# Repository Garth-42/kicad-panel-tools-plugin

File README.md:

# harness_engine

Generate wire-harness manufacturing docs from a KiCad design: a point-to-point
**wire list** (CSV), a **WireViz** harness diagram/BOM, and a **panel wiring
diagram** (SVG) drawn from the board itself — device outlines, wire-colored
runs, wire-number flags. The schematic/board stays the single source of truth;
the docs are generated, never hand-maintained.

Also in the box: a KiCad **project template** for 1:1 panel layouts (net
classes as wire types, colored/width-scaled tracks), the **Panel device**
footprint wizard + starter library for fast 2D device footprints, persistent
wire numbers, and a **PCM package** (`scripts/build_pcm.py`) for one-click
install. No third-party Python packages required (YAML reader bundled).

## Docs

**User guide** (GitHub Pages site, source in `docs/`):
[index](docs/index.md) · [installation](docs/installation.md) ·
[KiCad project setup / naming conventions](docs/kicad-setup.md) ·
[exporting CSV & WireViz](docs/exporting.md).
To host it: repo **Settings → Pages → Deploy from a branch → `main` + `/docs`**.

Developer docs:

- **`CLAUDE.md`** — architecture, conventions, testing, and the tested-vs-unverified matrix.
  Start here (also the Claude Code context file).
- **`docs/SPEC_SCHEMA.md`** — full `harness_specs.yaml` reference.
- **`docs/FREECAD_ROADMAP.md`** — the planned 3D / cut-length / formboard expansion.
- **`kicad_plugin/README.md`** — installing and using the pcbnew plugin.

## Two ways to run

**Board route** (pcbnew Action Plugin) — needs footprints; the only route that yields real
cut lengths. Copy `kicad_plugin/` and `harness/` into your KiCad plugin directory
(Tools → External Plugins → Open Plugin Directory), Refresh, then
Tools → External Plugins → **Generate harness docs**. Outputs land next to the board.

**Netlist route** (CLI) — no footprints needed; everything except length:

```
kicad-cli sch export netlist --format kicadxml -o design.net.xml design.kicad_sch
python -m harness design.net.xml --specs harness_specs.yaml --numbering group --wireviz out.yaml
```

Headless board run (KiCad's Python, from the repo root):

```
<kicad-python> -m kicad_plugin path/to/board.kicad_pcb
```

Both routes keep wire numbers stable across re-exports via `wire_numbers.json`
(written next to the board / netlist — commit it with the design). CLI:
`--numbers PATH` to relocate it, `--no-persist` to disable.

## Install

```
pip install -r requirements.txt        # just PyYAML
```
(The CSV path works without PyYAML; WireViz + spec-file loading need it. KiCad's bundled
Python often lacks it — YAML imports are lazy so the CSV still runs.)

## Tests

```
for t in tests/test_*.py; do python3 "$t"; done
```

## Quick mental model

`ingest/ (KiCad) -> engine (Connectivity + harness_specs.yaml) -> emit (CSV / WireViz)`.
Wire type comes from KiCad **net classes**; multi-conductor cables from **named group buses**
(`W5{L1 L2 L3}` -> nets `W5.L1…`); cut length from **routed track length**. See `CLAUDE.md`.

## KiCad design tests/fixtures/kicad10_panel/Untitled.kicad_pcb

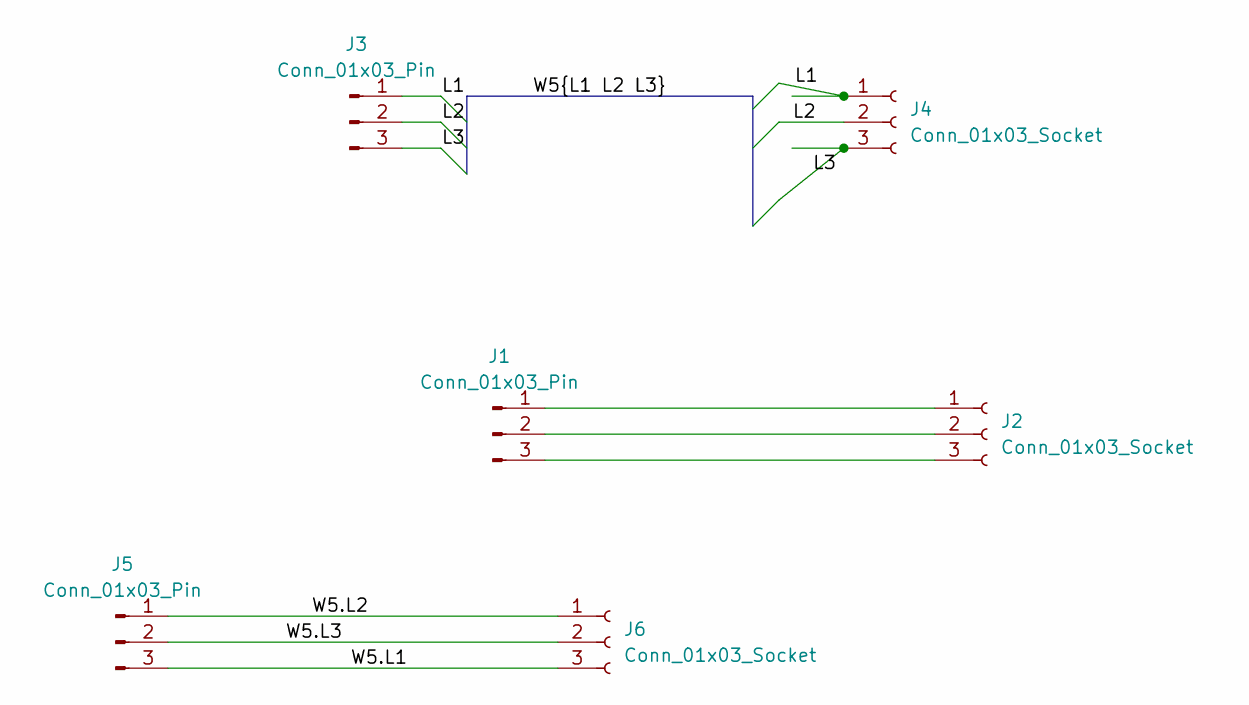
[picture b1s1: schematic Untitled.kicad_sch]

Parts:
J1, J3, J5: Conn_01x03_Pin; Molex_CLIK-Mate_502382-0370_1x03-1MP_P1.25mm_Vertical
J2, J4, J6: Conn_01x03_Socket; Molex_CLIK-Mate_502382-0370_1x03-1MP_P1.25mm_Vertical

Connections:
/L1: J3.1, J4.1
/L2: J3.2, J4.2
/L3: J3.3, J4.3
/W5.L1: J5.3, J6.3
/W5.L2: J5.1, J6.1
/W5.L3: J5.2, J6.2
unnamed: J1.1, J2.1
unnamed: J1.2, J2.2
unnamed: J1.3, J2.3

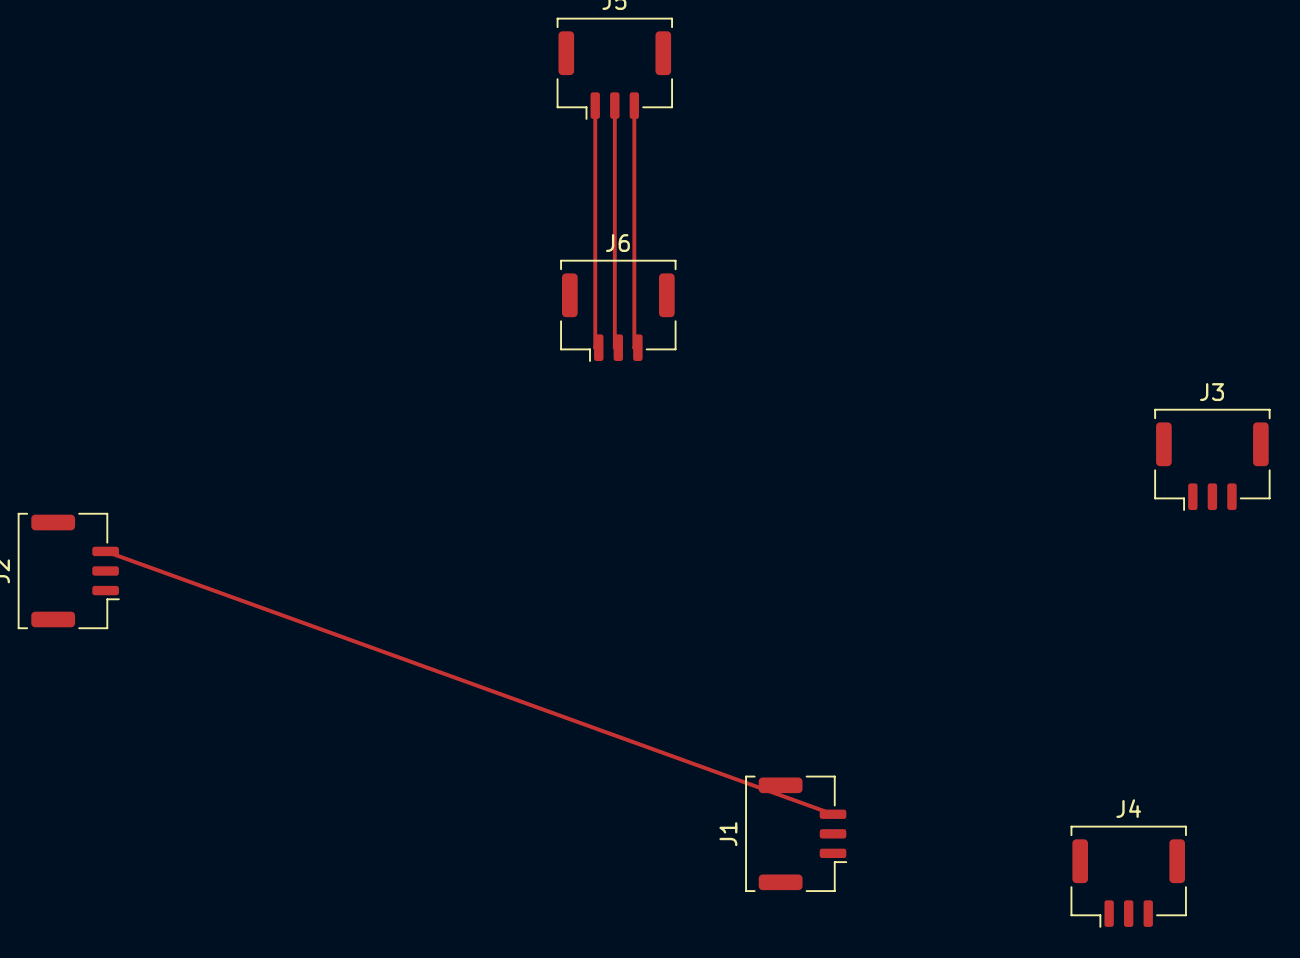
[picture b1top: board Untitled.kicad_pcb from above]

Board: 2 copper layers, 6 parts (0 on the bottom side), 9 nets.
